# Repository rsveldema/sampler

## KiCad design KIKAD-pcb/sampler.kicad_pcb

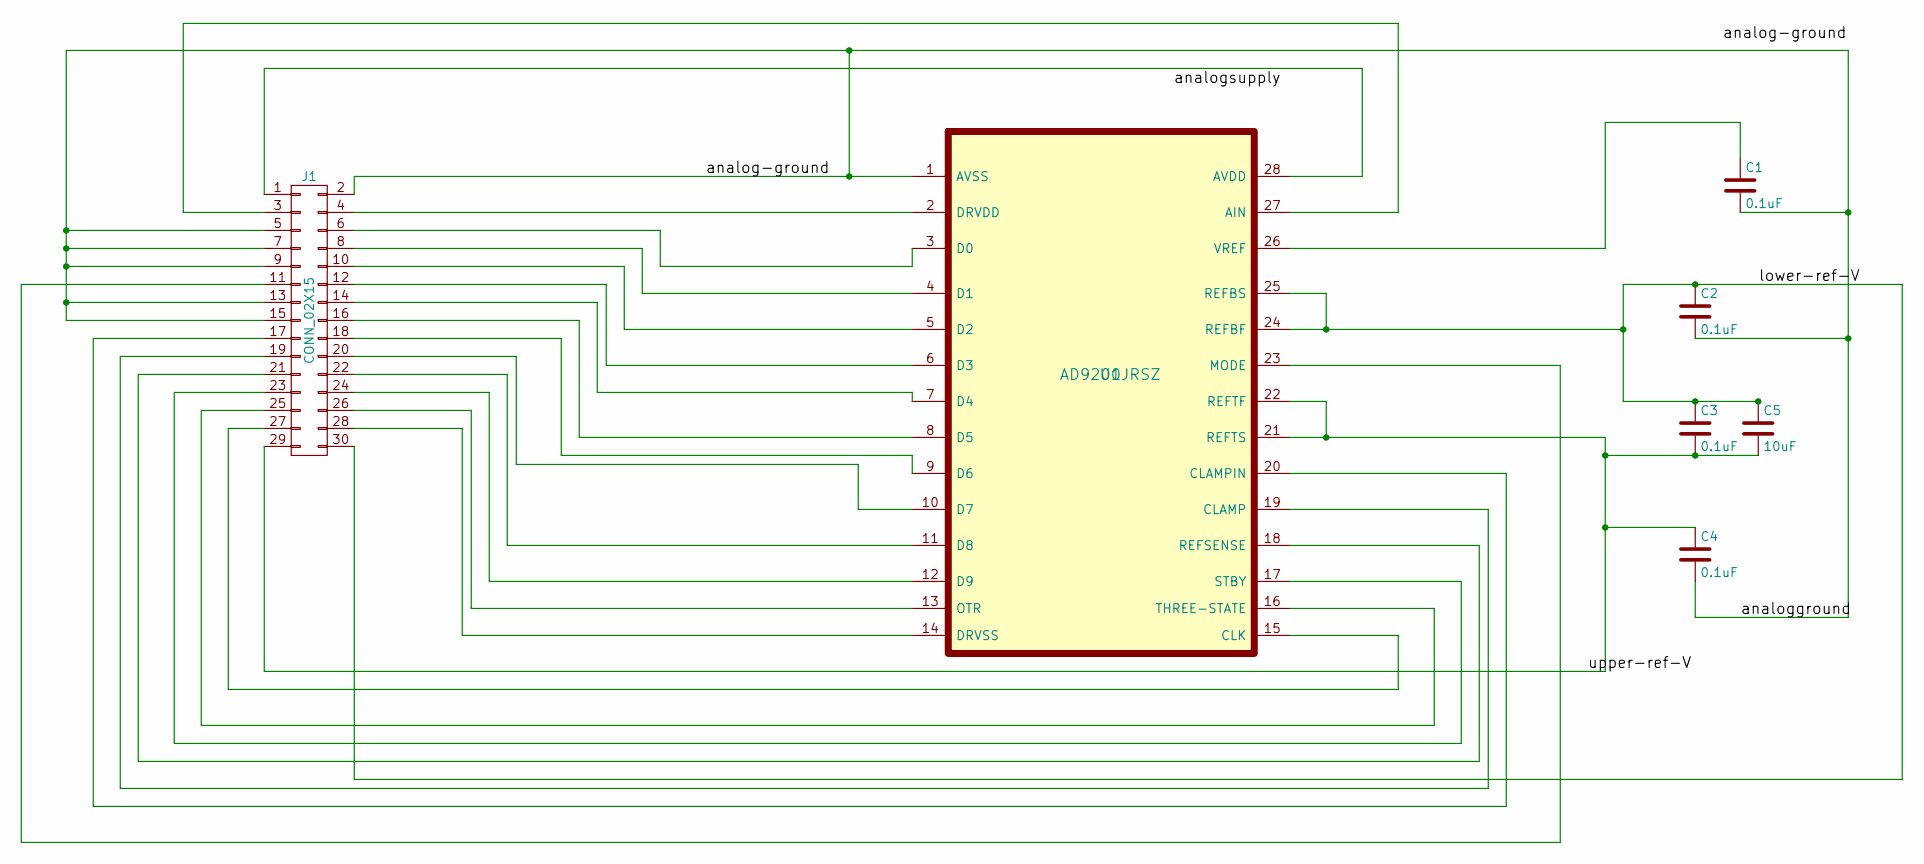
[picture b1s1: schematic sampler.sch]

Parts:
C1, C2, C3, C4: 0.1uF; C_0805
C5: 10uF; C_0603
J1: CONN_02X15; Pin_Header_Straight_2x15_Pitch2.54mm_SMD
U1: AD9200JRSZ; SSOP-28_5.3x10.2mm_Pitch0.65mm

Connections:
/analog-ground: C1.2, C2.2, C4.2, J1.2, J1.5, J1.7, J1.9, J1.13, J1.15, U1.1 (AVSS)
/lower-ref-V: C2.1, C3.1, C5.1, J1.30, U1.24 (REFBF), U1.25 (REFBS)
/upper-ref-V: C3.2, C4.1, C5.2, J1.29, U1.21 (REFTS), U1.22 (REFTF)
unnamed: C1.1, U1.26 (VREF)
unnamed: J1.1, U1.28 (AVDD)
unnamed: J1.3, U1.27 (AIN)
unnamed: J1.4, U1.2 (DRVDD)
unnamed: J1.6, U1.3 (D0)
unnamed: J1.8, U1.4 (D1)
unnamed: J1.10, U1.5 (D2)
unnamed: J1.11, U1.23 (MODE)
unnamed: J1.12, U1.6 (D3)
unnamed: J1.14, U1.7 (D4)
unnamed: J1.16, U1.8 (D5)
unnamed: J1.17, U1.20 (CLAMPIN)
unnamed: J1.18, U1.9 (D6)
unnamed: J1.19, U1.19 (CLAMP)
unnamed: J1.20, U1.10 (D7)
unnamed: J1.21, U1.18 (REFSENSE)
unnamed: J1.22, U1.11 (D8)
unnamed: J1.23, U1.17 (STBY)
unnamed: J1.24, U1.12 (D9)
unnamed: J1.25, U1.16 (THREE-STATE)
unnamed: J1.26, U1.13 (OTR)
unnamed: J1.27, U1.15 (CLK)
unnamed: J1.28, U1.14 (DRVSS)

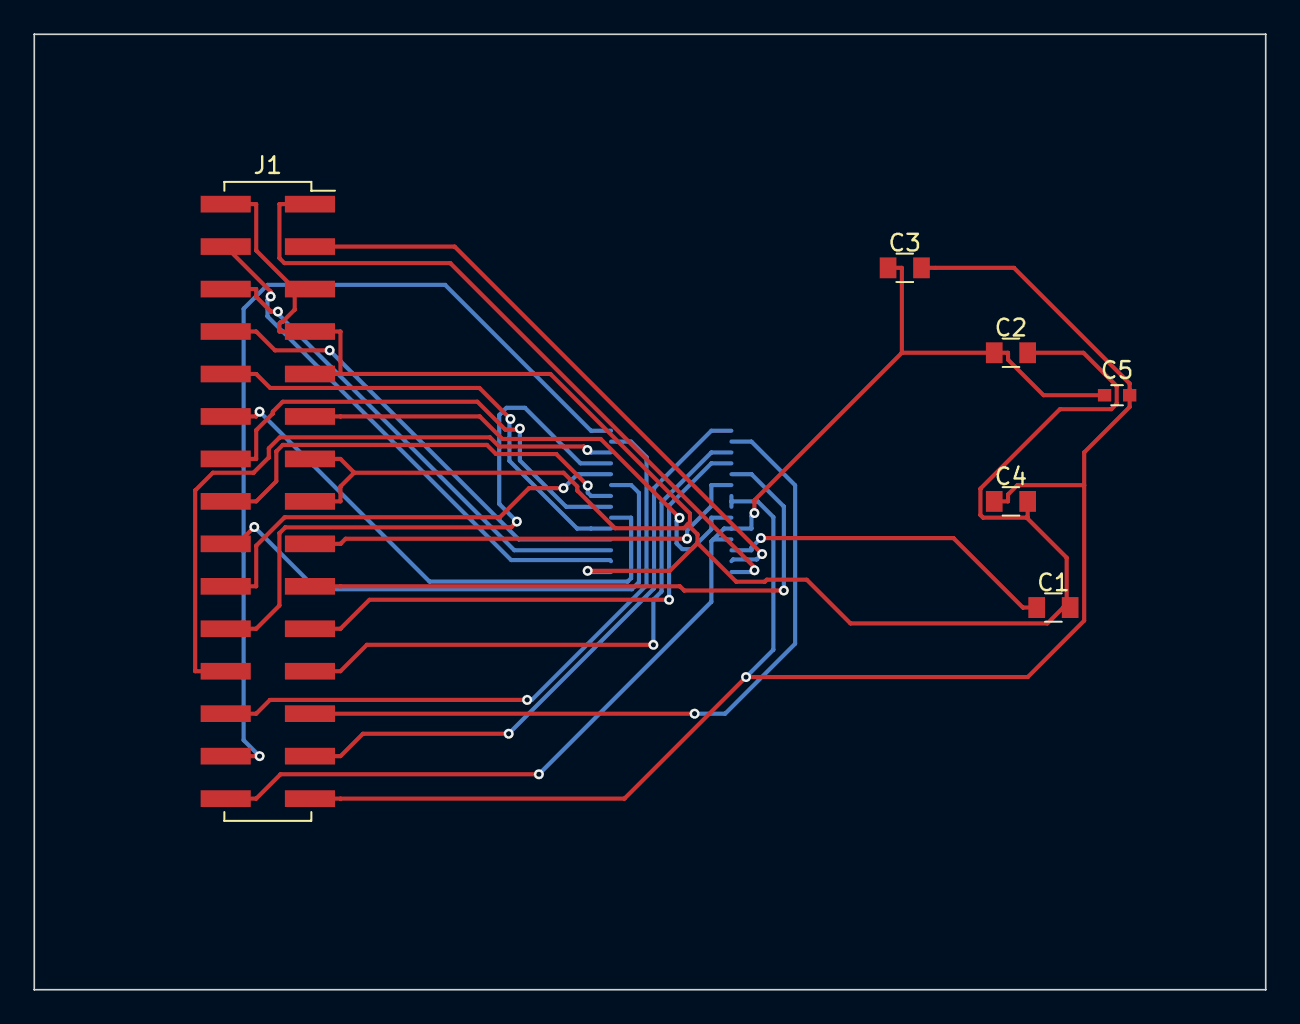
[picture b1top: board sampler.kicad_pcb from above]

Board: 2 copper layers, 73.7 x 57.2 mm, 7 parts (1 on the bottom side), 26 nets.

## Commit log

2017-06-15 - nios II with jtag-uart, local memory in qsys - niosII firmware with bsp with hello world
2017-06-25 LEDs work
2017-06-25 updated with sdram controller...
2017-06-25 sdram test works ok.
2017-06-25 sdram works.
2017-06-25 missing files `
2017-08-06 - datasheet added - start at PCB description with ki-cad
2017-08-06 pcb bugfix.
2017-08-06 picked footprints
2017-08-10 pcb update
2017-08-12 autoplaced
2017-09-26 next attempt with eagle
2017-10-22 updated schematic, 1st try at board
2017-11-01 updated autocad's Eagle files, latest is schematic with PCB with GND-added.
